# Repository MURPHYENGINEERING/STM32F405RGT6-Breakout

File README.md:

# Phil's STM32F4 Breakout board
Following along with [this excellent video](https://www.youtube.com/watch?v=t5phi3nT8OU) from [Phil's Lab](https://www.youtube.com/channel/UCVryWqJ4cSlbTSETBHpBUWw)

Also check out his very cool [fixed wing](http://philsal.co.uk/projects/uav/fixed-wing-flight-control-system) and [multirotor projects](http://philsal.co.uk/projects/uav/hadesmicro-quadcopter-flight-control-system).

[Please consider supporting his work by becoming a patron.](https://www.patreon.com/phils94)

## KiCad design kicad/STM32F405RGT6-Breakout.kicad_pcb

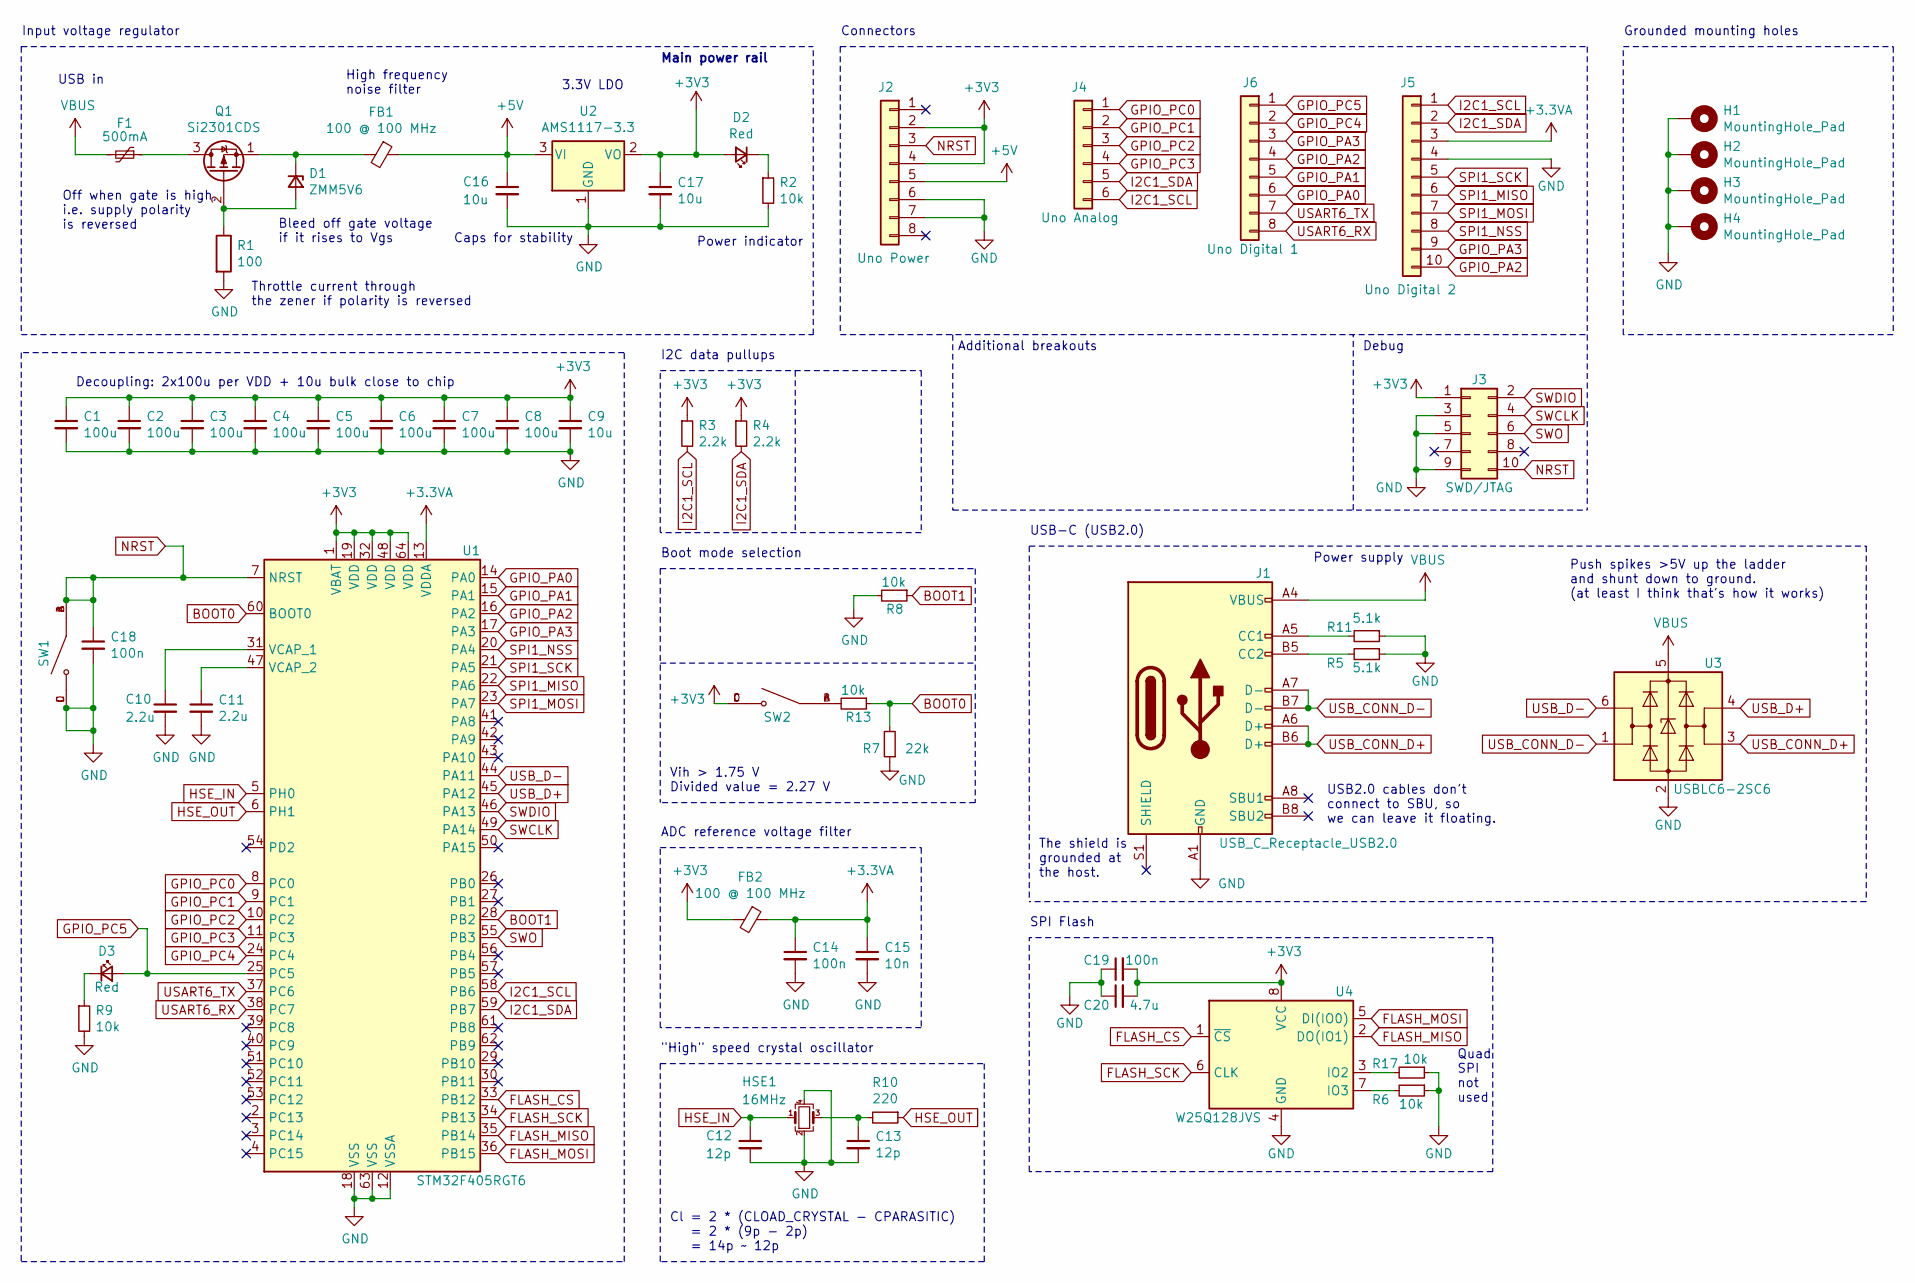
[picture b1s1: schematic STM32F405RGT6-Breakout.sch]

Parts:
C1, C2, C3, C4, C5, C6, C7, C8: 100u; C_0402_1005Metric
C9: 10u; C_0603_1608Metric
C10, C11: 2.2u; C_0603_1608Metric
C12, C13: 12p; C_0402_1005Metric
C14, C18: 100n; C_0402_1005Metric
C15: 10n; C_0402_1005Metric
C16, C17: 10u; C_0805_2012Metric
C19: 100n; C_0603_1608Metric
C20: 4.7u; C_0805_2012Metric
D1: ZMM5V6; D_MiniMELF
D2, D3: Red; D_0603_1608Metric
F1: 500mA; Fuse_0603_1608Metric
FB1, FB2: 100 @ 100 MHz; L_0805_2012Metric; JLCPCB Part C1015
H1, H2, H3, H4: MountingHole_Pad; MountingHole_3.2mm_M3_Pad_Via
HSE1: 16MHz; Crystal_SMD_3225-4Pin_3.2x2.5mm; JLCPCB Part C160456
J1: USB_C_Receptacle_USB2.0; USB_C_Receptacle_XKB_U262-16XN-4BVC11; JLCPCB Part C319148
J2: Uno Power; PinSocket_1x08_P2.54mm_Vertical_SMD_Pin1Left
J3: SWD/JTAG; PinHeader_2x05_P1.27mm_Vertical_SMD
J4: Uno Analog; PinSocket_1x06_P2.54mm_Vertical_SMD_Pin1Left
J5: Uno Digital 2; PinSocket_1x10_P2.54mm_Vertical_SMD_Pin1Left
J6: Uno Digital 1; PinSocket_1x08_P2.54mm_Vertical_SMD_Pin1Left
Q1: Si2301CDS; SOT-23; JLCPCB Part C10487
R1: 100; R_0805_2012Metric
R2, R9: 10k; R_0603_1608Metric
R3, R4: 2.2k; R_0402_1005Metric
R5, R11: 5.1k; R_0402_1005Metric
R6, R8, R13, R17: 10k; R_0402_1005Metric
R7: 22k; R_0603_1608Metric
R10: 220; R_0402_1005Metric
SW1, SW2: TS-1187A-B-A-B; SW_TS-1187A-B-A-B; PARTREV A0; JLCPCB Part C318884
U1: STM32F405RGT6; LQFP-64_10x10mm_P0.5mm; JLCPCB Part C15742
U2: AMS1117-3.3; SOT-223-3_TabPin2; JLCPCB Part C6186
U3: USBLC6-2SC6; SOT-23-6; JLCPCB Part C2827654
U4: W25Q128JVS; SOIC-8_5.23x5.23mm_P1.27mm; JLCPCB Part C97521

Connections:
+3.3VA: C14.1, C15.1, FB2.1, J5.3, U1.13 (VDDA)
+3V3: C1.1, C2.1, C3.1, C4.1, C5.1, C6.1, C7.1, C8.1, C9.1, C17.1, C19.2, C20.2, D2.2 (A), FB2.2, J2.2, J2.4, J3.1, R3.1, R4.1, SW2.C, SW2.D, U1.1 (VBAT), U1.19 (VDD), U1.32 (VDD), U1.48 (VDD), U1.64 (VDD), U2.2 (VO), U4.8 (VCC)
+5V: C16.1, FB1.1, J2.5, U2.3 (VI)
BOOT0: R7.2, R13.1, U1.60 (BOOT0)
BOOT1: R8.1, U1.28 (PB2)
FLASH_CS: U1.33 (PB12), U4.1 (~CS)
FLASH_MISO: U1.35 (PB14), U4.2 (DO(IO1))
FLASH_MOSI: U1.36 (PB15), U4.5 (DI(IO0))
FLASH_SCK: U1.34 (PB13), U4.6 (CLK)
GND: C1.2, C2.2, C3.2, C4.2, C5.2, C6.2, C7.2, C8.2, C9.2, C10.2, C11.2, C12.2, C13.2, C14.2, C15.2, C16.2, C17.2, C18.2, C19.1, C20.1, H1.1, H2.1, H3.1, H4.1, HSE1.2, HSE1.4, J1.A1 (GND), J1.A12 (GND), J1.B1 (GND), J1.B12 (GND), J2.6, J2.7, J3.3, J3.5, J3.9, J5.4, R1.2, R2.2, R5.1, R6.1, R7.1, R8.2, R9.2, R11.1, R17.1, SW1.C, SW1.D, U1.12 (VSSA), U1.18 (VSS), U1.63 (VSS), U2.1 (GND), U3.2 (GND), U4.4 (GND)
GPIO_PA0: J6.6, U1.14 (PA0)
GPIO_PA1: J6.5, U1.15 (PA1)
GPIO_PA2: J5.10, J6.4, U1.16 (PA2)
GPIO_PA3: J5.9, J6.3, U1.17 (PA3)
GPIO_PC0: J4.1, U1.8 (PC0)
GPIO_PC1: J4.2, U1.9 (PC1)
GPIO_PC2: J4.3, U1.10 (PC2)
GPIO_PC3: J4.4, U1.11 (PC3)
GPIO_PC4: J6.2, U1.24 (PC4)
GPIO_PC5: D3.2 (A), J6.1, U1.25 (PC5)
HSE_IN: C12.1, HSE1.1, U1.5 (PH0)
HSE_OUT: R10.1, U1.6 (PH1)
I2C1_SCL: J4.6, J5.1, R3.2, U1.58 (PB6)
I2C1_SDA: J4.5, J5.2, R4.2, U1.59 (PB7)
NRST: C18.1, J2.3, J3.10, SW1.A, SW1.B, U1.7 (NRST)
unnamed: C10.1, U1.31 (VCAP_1)
unnamed: C11.1, U1.47 (VCAP_2)
unnamed: C13.1, HSE1.3, R10.2
unnamed: D1.1 (K), FB1.2, Q1.1 (S)
unnamed: D1.2 (A), Q1.2 (G), R1.1
unnamed: D2.1 (K), R2.1
unnamed: D3.1 (K), R9.1
unnamed: F1.1, Q1.3 (D)
unnamed: J1.A5 (CC1), R11.2
unnamed: J1.B5 (CC2), R5.2
unnamed: R6.2, U4.7 (IO3)
unnamed: R13.2, SW2.A, SW2.B
unnamed: R17.2, U4.3 (IO2)
SPI1_MISO: J5.6, U1.22 (PA6)
SPI1_MOSI: J5.7, U1.23 (PA7)
SPI1_NSS: J5.8, U1.20 (PA4)
SPI1_SCK: J5.5, U1.21 (PA5)
SWCLK: J3.4, U1.49 (PA14)
SWDIO: J3.2, U1.46 (PA13)
SWO: J3.6, U1.55 (PB3)
USART6_RX: J6.8, U1.38 (PC7)
USART6_TX: J6.7, U1.37 (PC6)
USB_CONN_D+: J1.A6 (D+), J1.B6 (D+), U3.3 (I/O2)
USB_CONN_D-: J1.A7 (D-), J1.B7 (D-), U3.1 (I/O1)
USB_D+: U1.45 (PA12), U3.4 (I/O2)
USB_D-: U1.44 (PA11), U3.6 (I/O1)
VBUS: F1.2, J1.A4 (VBUS), J1.A9 (VBUS), J1.B4 (VBUS), J1.B9 (VBUS), U3.5 (VBUS)

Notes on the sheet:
Throttle current through the zener if polarity is reversed
Bleed off gate voltage if it rises to Vgs
Caps for stability
High frequency noise filter
3.3V LDO
Cl = 2 * (CLOAD_CRYSTAL - CPARASITIC) = 2 * (9p - 2p) = 14p ~~ 12p
ADC reference voltage filter
Input voltage regulator
"High" speed crystal oscillator
Decoupling: 2x100u per VDD + 10u bulk close to chip
Off when gate is high, i.e. supply polarity is reversed
Connectors
I2C data pullups
Grounded mounting holes
Power indicator
USB in
Main power rail
The shield is grounded at the host.
USB-C (USB2.0)
USB2.0 cables don't connect to SBU, so we can leave it floating.
Push spikes >5V up the ladder and shunt down to ground. (at least I think that's how it works)
Quad SPI not used
SPI Flash
Boot mode selection
Power supply
Vih > 1.75 V Divided value = 2.27 V
Debug
Additional breakouts

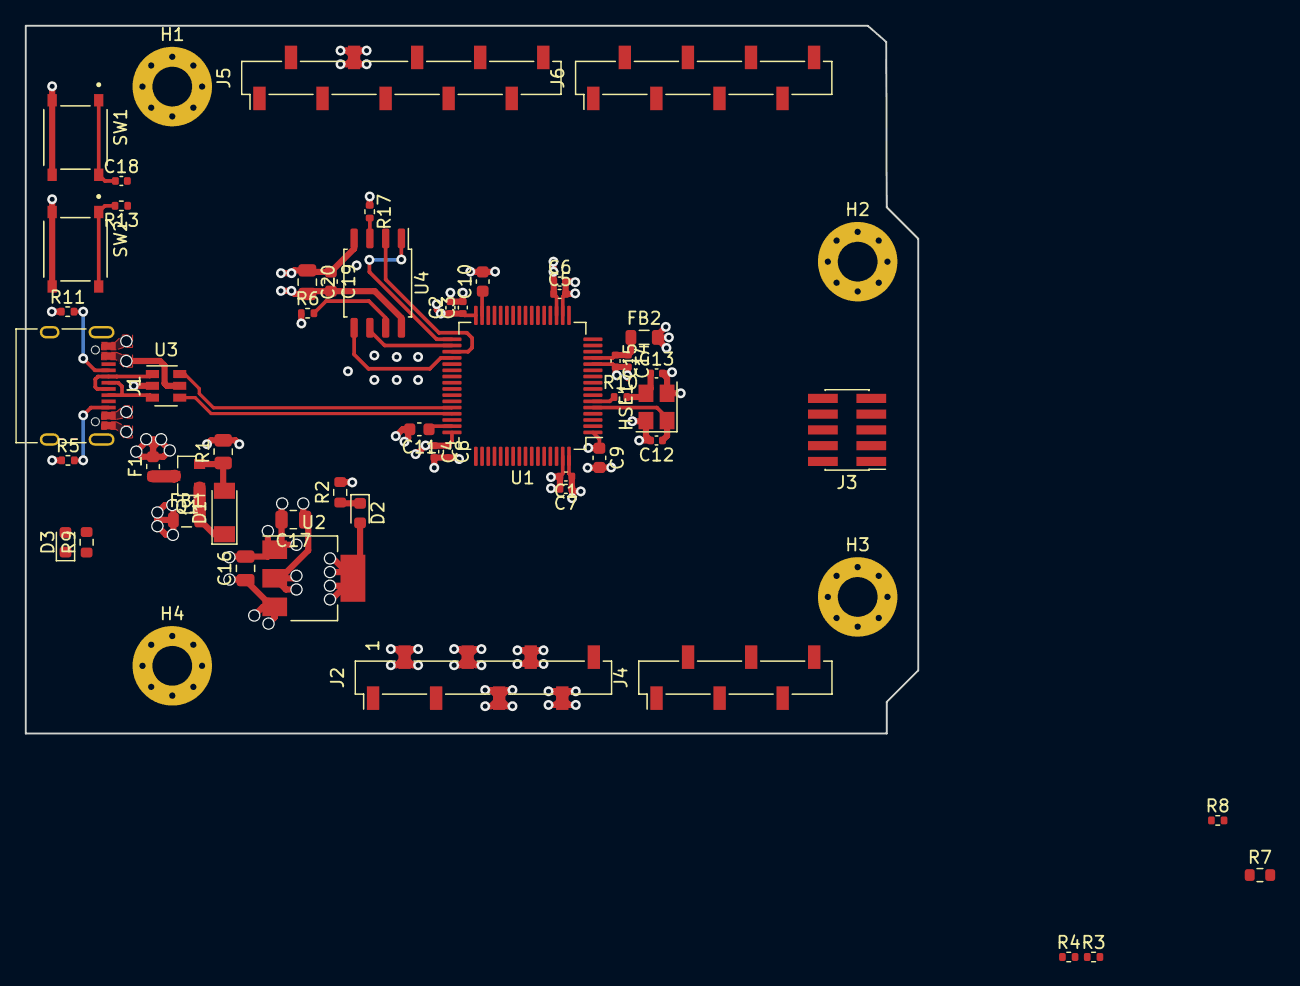
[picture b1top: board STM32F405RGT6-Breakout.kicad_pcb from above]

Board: 4 copper layers, 71.9 x 57.0 mm, 57 parts (0 on the bottom side), 52 nets.

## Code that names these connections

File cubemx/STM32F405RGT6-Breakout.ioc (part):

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Mcu.Name=STM32F405RGTx
Mcu.Package=LQFP64
Mcu.UserName=STM32F405RGTx
PA0-WKUP.Mode=SYS_WakeUp0
PA0-WKUP.Signal=SYS_WKUP
PA11.Mode=Device_Only
PA11.Signal=USB_OTG_FS_DM
PA12.Mode=Device_Only
PA12.Signal=USB_OTG_FS_DP
PA13.Mode=Trace_Asynchronous_SW
PA13.Signal=SYS_JTMS-SWDIO
PA14.Mode=Trace_Asynchronous_SW
PA14.Signal=SYS_JTCK-SWCLK
PA4.Mode=NSS_Signal_Hard_Output
PA4.Signal=SPI1_NSS
PA5.Mode=Full_Duplex_Master
PA5.Signal=SPI1_SCK
PA6.Mode=Full_Duplex_Master
PA6.Signal=SPI1_MISO
PA7.Mode=Full_Duplex_Master
PA7.Signal=SPI1_MOSI
PB10.Mode=I2C
PB10.Signal=I2C2_SCL
PB11.Mode=I2C
PB11.Signal=I2C2_SDA
PB12.GPIOParameters=GPIO_Label
PB12.GPIO_Label=FLASH_CS
PB12.Mode=NSS_Signal_Hard_Output
PB12.Signal=SPI2_NSS
PB13.GPIOParameters=GPIO_Label
PB13.GPIO_Label=FLASH_SCK
PB13.Mode=Full_Duplex_Master
PB13.Signal=SPI2_SCK
PB14.GPIOParameters=GPIO_Label
PB14.GPIO_Label=FLASH_MISO
PB14.Mode=Full_Duplex_Master
PB14.Signal=SPI2_MISO
PB15.GPIOParameters=GPIO_Label
PB15.GPIO_Label=FLASH_MOSI
PB15.Mode=Full_Duplex_Master
PB15.Signal=SPI2_MOSI
PB3.Mode=Trace_Asynchronous_SW
PB3.Signal=SYS_JTDO-SWO
PB6.Mode=I2C
PB6.Signal=I2C1_SCL
PB7.Mode=I2C
PB7.Signal=I2C1_SDA
PC6.Mode=Asynchronous
PC6.Signal=USART6_TX
PC7.Mode=Asynchronous
PC7.Signal=USART6_RX
PH0-OSC_IN.GPIOParameters=GPIO_Label
PH0-OSC_IN.GPIO_Label=HSE_IN
PH0-OSC_IN.Mode=HSE-External-Oscillator
PH0-OSC_IN.Signal=RCC_OSC_IN
PH1-OSC_OUT.GPIOParameters=GPIO_Label
PH1-OSC_OUT.GPIO_Label=HSE_OUT
PH1-OSC_OUT.Mode=HSE-External-Oscillator
PH1-OSC_OUT.Signal=RCC_OSC_OUT
RCC.HSE_VALUE=16000000
RCC.SYSCLKFreq_VALUE=16000000
board=custom

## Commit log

2021-11-13 plugs
2021-11-13 KiCad project
2021-11-15 Input voltage regulator with pch input reverse polarity protection
2021-11-15 ADC voltage reference filter
2021-11-15 decoupling
2021-11-15 boot mode pins
2021-11-15 Configure pins for high speed crystal
2021-11-15 Crystal oscillator
2021-11-15 Hook up serial wire debug & enable on chip
2021-11-15 fixed an unconnected pin
2021-11-15 - add JTAG/SWD connector - configure USB pins on chip
2021-11-15 communication pins labeled
2021-11-16 - i2c pullups - connectors laid out - added 3v3 and gnd to i2c connectors - working on adding USB
2021-11-16 get rid of Vin, we'll use USB only
2021-11-16 - USB-C connector wired in with ESD protection. - We can't get the USBLC6-2SC6 chip except in full reels, so sub in the IP4220CZ6 (https://datasheet.lcsc.com/lcsc/1810121050_Nexperia-IP4220CZ6,125_C2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
    - Still looking for a USB connector that's available in 1+ qty and has a footprint we can get
2021-11-16 the power flags thing is stupid
2021-11-16 - Start assigning footprints for the major components o I was wrong about the pricing at JLCPCB; we don't have to buy a reel to do board assembly. - Still need to work out sizes for passives based on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
2021-11-20 Built-in bootloader docs for maybe flashing a more arduino-friendly bootloader
2021-11-20 Application notes
2021-11-20 MCU datasheet
2021-11-20 STM32CubeProgrammer user guide
2021-11-20 USBLC6: USB ESD protection datasheet
2021-11-20 Tech public mfg. datasheet for USB ESD protection
2021-11-20 Reduced the size of the title block
2021-11-20 Started adding a 128mb NOR flash, but eh... why? They're basic parts at JLCPCB so it might be worth it just to try interfacing with it and see what's going on there. It seems pretty idiot proof hardw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
2021-11-20 Added a demo of entering DFU straight from user code. We might end up requiring some user code that scans USB for a magic code that either starts DFU or ruins your project because the magic code appe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
2021-11-20 why wasn't this in gitignore already -_-
2021-11-20 clarify what software the board files are for
2021-11-21 Application note for SPI flash decoupling
2021-11-21 - Added onboard SPI flash, just to experiment with (128mb NOR flash is basic part at JLCPCB) - Added momentary switches for BOOT0 and NRST to get into DFU mode, like the black pill - Added a capacito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
2021-11-21 nix the SD card slot, I can't imagine trying to route that right now
2021-11-21 Half way done with footprint assignment
2021-11-21 USB connector datasheet
2021-11-21 - Added SPST tact switch symbol & footprint from JLPCB - Used SPST to ground NRST for reset - Used SPST to raise BOOT0 for DFU - BOOT0 on voltage divider, should work with the switch bringing BOOT0 t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
2021-11-21 Rough layout functional groups
2021-11-21 - Laid out & routed crystal - Laid out & started routing MCU decoupling
    --> Checkpoint before trying new flash orientation
2021-11-21 This flash SPI routing is definitely better
2021-11-22 - USB connector & ESD protection laid out - Crystal moved to make room for fanning out GPIO pins
2021-11-22 - Lots of GPIO breakouts wired up - Lots of signal isolation vias that I'm completely guessing about
    Still to lay out and route: power, USB, UART, SWD
2021-11-22 Checkpoint before starting over because too many afterthoughts piling up wrt. connectors
2021-11-22 Adopting the constraint of Arduino Uno shield compatibility to narrow the design choices a bit
2021-11-22 Remapped to Uno headers
2021-11-22 - Laid out headers by Uno template - Basic functional component layout - Fixed USB connector clearances to get rid of warnings
2021-11-22 Crystal ground
2021-11-22 MCU decoupling
2021-11-22 Start cutting out 5V plane
2021-11-22 lol, all my via pads were too small
2021-11-22 lol, I learned what thermal relief is
2021-11-23 SPI flash routed
2021-11-23 First ever attempt at actual routing, it went terribly
2021-11-23 Revert "First ever attempt at actual routing, it went terribly"
    This reverts commit ef1419a7460263513f620155a18387d495a8f3db.
    lol
2021-11-23 run the SPI flash CS a little shorter on the bottom
